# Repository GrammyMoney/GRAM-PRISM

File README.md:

# GRAM PRI$M

# Introduction 
The **PRI$M** is a modular take on the Prism, originally designed by WunWae. It has the standard pinout for firmwares like HayBox and Pico-Rectangle, and is also compatible with more fleshed-out FGC firmwares like GP2040-CE. The key distinctive features between the original Prism and the PRI$M is the USB-C connectivity, and the modular panels that can be replaced and swapped to change the hand layouts without purchasing a whole new controller. With industrial design from GRAM, PCB designed by Quark.Works, this guide goes over a DIY-friendly approach to building and modifying the PRI$M to suit your needs.

**If you would like to support the developers of this project, consider purchasing parts like buttons, PCBs, USB-C to GCC cables, and official GRAM builds at [GRAMCTRL.COM](https://www.gramctrl.com) rather than a fab house.**

Included Files
-
Included in this repo is all the files needed to get started with a PRI$M build:
- **PRI$M Frame .stl files**
- **Aluminum Panel** Gerber files *(5 of 'em!)*
- **PCB Gerbers** for multiple hand layouts and a panelized version for the standard layout

Additional Information
-
If you want more info around GRAM builds, both open source and official builds, please join the [GRAM Digital Controllers Discord](https://discord.gg/6TuHw2r2X4) to ask questions and work with the community! I would love to see people creating new interesting designs, and building upon our initial framework.

Thanks & Acknowledgements
-
There are several people who made this project possible, either directly or indirectly.
- [Quark](https://twitter.com/quark_works), who did the PCB design on this and many other GRAM projects.
- [WunWae](https://twitter.com/WuhnWae), who developed the ergonomics and original Prism design. Thank you for your blessing on this crazy project!
- My life and business partner [BRUISES](https://twitter.com/bruisesxo), who has turned GRAM into what it is today, and had incredible patience with me as I toiled away at my computer late into the night designing this thing.

# Ordering & Customization Guide
While most of these files are universal and can be used at any fab house, **JLCPCB** has become the de-facto standard for DIY box manufacturing. This is due to their hyper-affordable pricing and low minimum order quantity.

Bill of Materials
-
Per GRAM PRI$M, you will need (some files can be made using this repository, but I will link to places to purchase them if you would like to avoid MOQs)
- 1 x PRI$M PCB set *(either panelized, or individual PCBs)*
- 1 x set of PRI$M Aluminum Panels
- 20 x [Kailh Choc V1 switches](https://www.moergo.com/products/kailh-choc-v1-key-switches-red-brown-white-pro-red-20-pack?variant=45328736780561) (Red, Red Pro, and Whites are all great choices)
- 20 x [PG1350 Hotswap Sockets](https://mkultra.click/kailh-hotswap-sockets)
- 20 x Choc v1 keycaps *(I recommend MBK profile)*
- 1 x GRAM PRI$M Frame
- 8 x [M5x0.8 8mm Low-Profile Socket Head Screws](https://www.mcmaster.com/92855A507)
- 2 x [M2.5x0.45 4mm Button Head Screws](https://www.mcmaster.com/catalog/130/3434/97763A412)
- 1 x [4" JST 6-pin Socket to Socket Reversed cable assembly](https://www.digikey.com/en/products/detail/jst-sales-america-inc/A06SR06SR30K102A/9922193)
- 1 x [4" 14-pin FPC Cable](https://www.digikey.com/en/products/detail/molex/0152670295/4427171)

*Optional*
- USB-C to GCC cable for console/adapter play

Tools Needed
-
This guide assumes a level of knowledge on soldering and computer literacy. General tool requirements are:
- Soldering iron
- Solder
- USB-C to USB-A cable
- 3mm hex key/allen wrench
- Pliers
- Patience :)

The PCB
-
***Note: Since the ordering process of the PRI$M is almost identical to the [SLIM](https://github.com/GrammyMoney/GRAM-SLIM), I have used the ordering guide from the SLIM here. You may need to do more repetitions of these steps depending on which PCB you are printing, and you need to do the panel steps for all 5 aluminum panels.***

The PCB Fabrication files should come in the form of a *Gerber ZIP file* and *bom/cpl files* (usually in Excel spreadsheet formats).

Drag them into the "Upload Gerbers" box at JLCPCB and this page will pop up:

Here you can change the color of the PCB. Green is the fastest and cheapest from JLC, but their black PCBs look *siiiiiick*. The only setting I recommend you change is to check "**Yes**" on *Confirm Production file*. This allows for any mistakes to be ironed out by their engineers.

Towards the bottom of the page, you want to turn on the switch for **PCB ASSEMBLY**.

Make sure you are assembling the *Bottom Side* of the PCB, and make sure to set *Confirm Parts Placement* to "**Yes**". None of the advanced options need to be changed.

Upon confirming your PCB Assembly options, you'll be taken to the Assembly wizard. Clicking next will give you a location to upload the *BOM* and *CPL* files (*CPL* is referred to as *Positions* in the GRAM Slim files). Once you click through, you'll be brought to you BOM list.

This will allow you to modify parts if there's any low stock. There's a line at the bottom for CH1-CH21 with some red text. This is for assembling hotswap sockets, which is not recommended for JLC, as you have to preorder them. when you click **next**, continue by clicking *Do not place*.

The wizard looks intimidating, but good news! Since you're confirming part placement, the JLC engineers will fix any errors. Just go ahead and continue.

There you have it! Your PCB is ready to order. As of the time of this writing, a set of 5 assembled boards costs $56.07 before shipping.

The Panels
-
The process of ordering aluminum panels from JLC is similar to the PCB ordering process, but much simpler. Start by dragging the **GRAM Slim Top** Zip file into the JLC upload window. We want an aluminum PCB, 1.6mm. You can choose either white or black coating (white tends to be glossy, black is matte but a fingerprint magnet). 

Under High-spec Options, make sure to remove order number, or else they'll put an ugly serial number on the panel.

Once you save to cart, you'll see this screen:

Here you can add the **GRAM Slim Bottom** Zip file, and it will copy all your settings from the Top panel. Save to cart, and you're ready to check out with your PCBs!

*Note: JLCPCB cannot transact PCB and 3D printing orders together, so place this order, then move on to 3D printing.*

The Frame
-
The frame file is pretty self explanatory. Just go into JLC's 3D printing section, drop the STL file in, and choose your material. I recommend black Resin, but LEDO 6060 is a great, low cost alternative. The only material I recommend against is the textured Nylon options, as the tolerances between the frame and panels are extremely tight, and the texture could interfere with that. make sure the surface finish is set to *sanded*. 

The website will flag some possible errors (Inverted normals, Multi-shells, Possible noise shells) but if you have not modified the .stl file you are good to go. It is also possible that their support contact you about a risk of deformation given the geometry of the workpiece but it is normal and you should reply to the email that you accept the risks.

Need help building your PRI$M? Feel free to join our [Discord](https://discord.gg/gramctrl) for advice from our lovely open source community!

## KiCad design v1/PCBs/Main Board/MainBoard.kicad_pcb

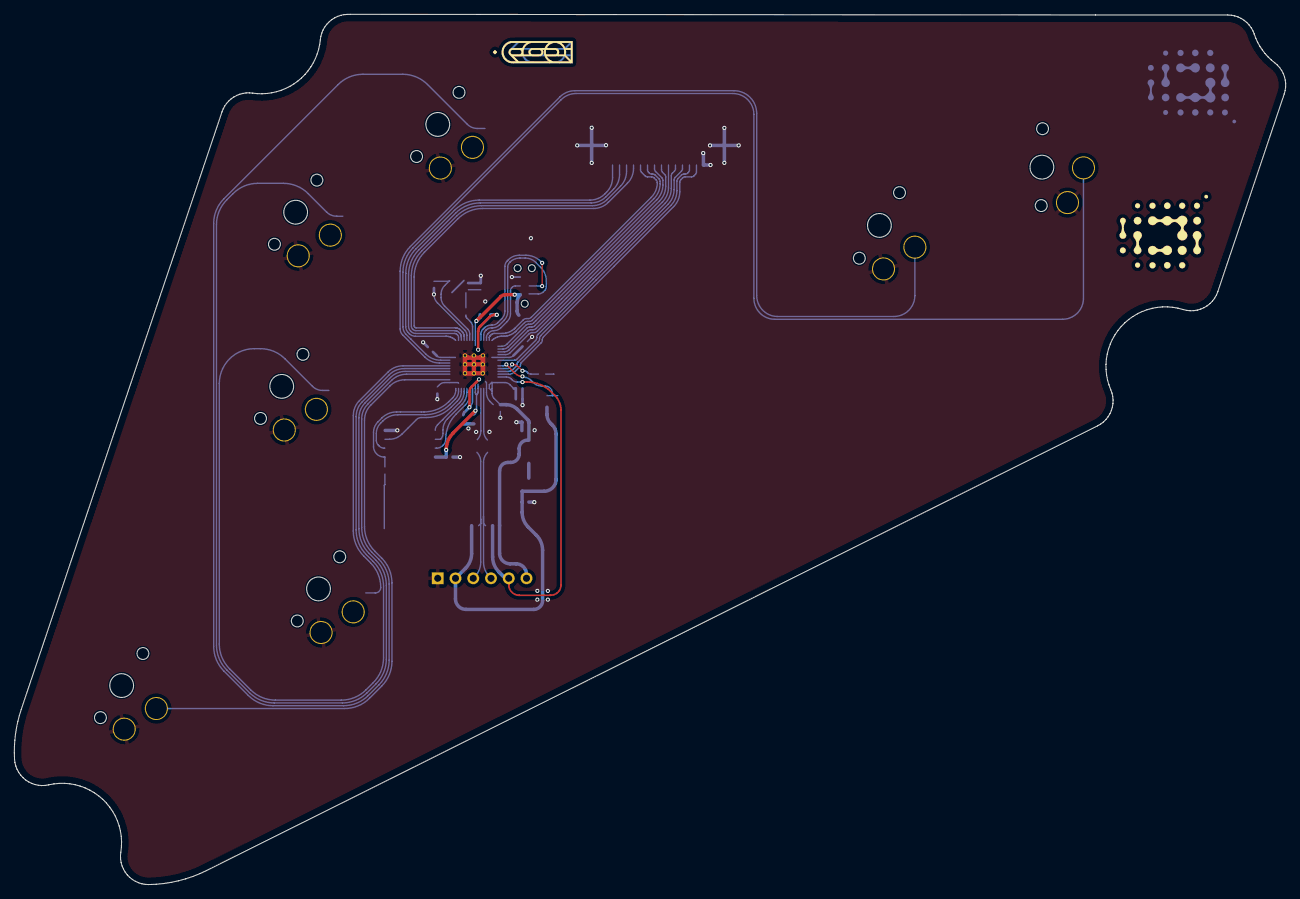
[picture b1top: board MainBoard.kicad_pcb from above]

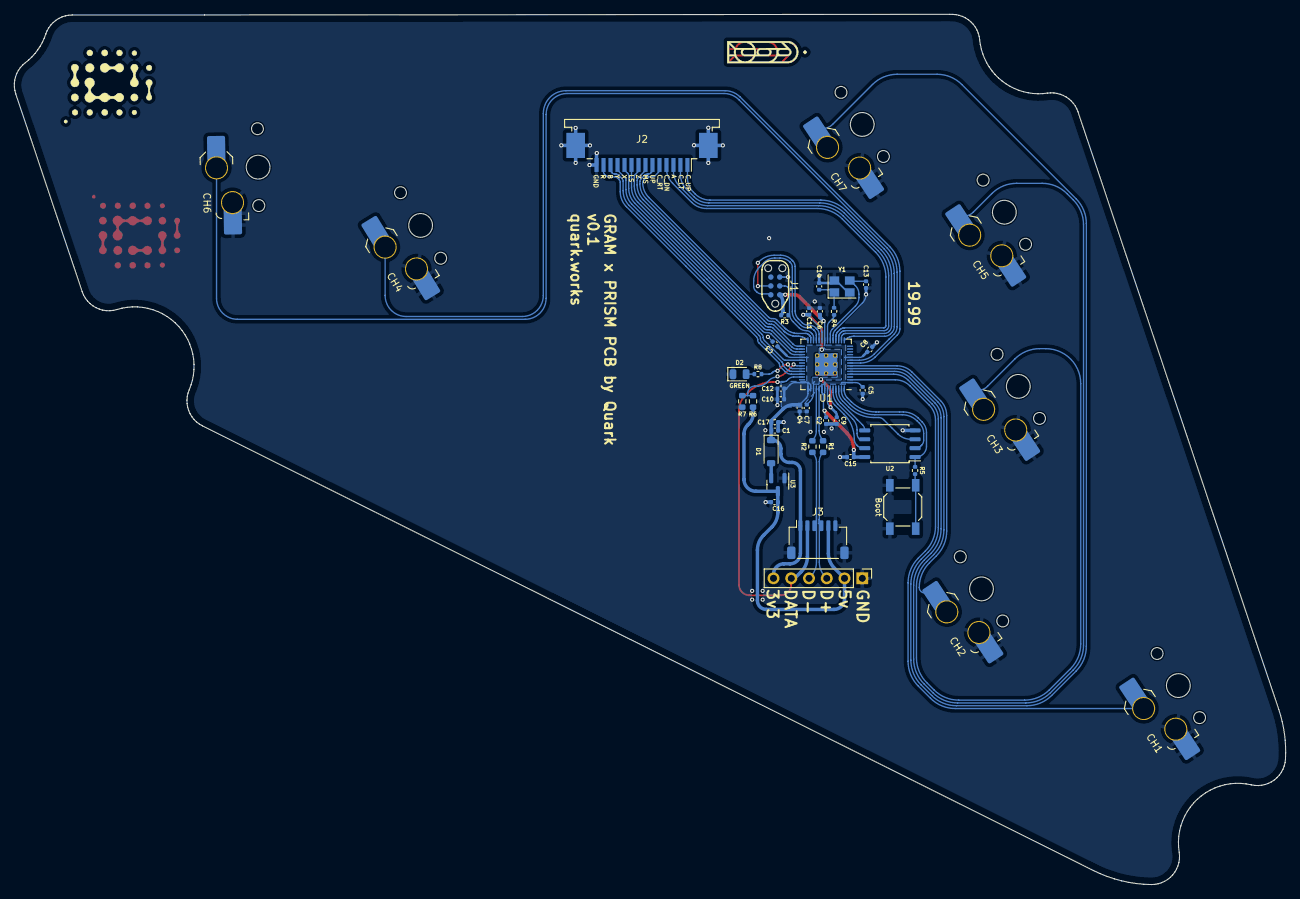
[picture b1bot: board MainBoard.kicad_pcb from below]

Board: 2 copper layers, 181.9 x 124.5 mm, 47 parts (45 on the bottom side), 46 nets.

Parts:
C1: 10uF; C_0402_1005Metric
C2, C7, C16, C17: 1uF; C_0402_1005Metric
C3, C4, C5, C6, C8, C9, C10, C11, C12, C15: 100nF; C_0402_1005Metric
C13, C14: 22pF; C_0402_1005Metric
CH1, CH2, CH3, CH4, CH5, CH6, CH7: choc_SW_HS; SW_choc_v1_HS_1u
D1: Schottky Diode; D_SOD-123
D2: GREEN; LED_0805_2012Metric
H1, H2: qw-logo; qw new logo silk + copper md
H3, H4: 19.99 logo; 1999 logo md
J1: JTAG_TC2030; CON_TC2030_outlined
J2: FFC Connector; TE_1-84953-4_1x14-1MP_P1.0mm_Horizontal
J3: JST Connector; JST_SH_SM06B-SRSS-TB_1x06-1MP_P1.00mm_Horizontal
J4: DuPont Connector; PinHeader_1x06_P2.54mm_Vertical
R1, R2: 27; R_0603_1608Metric
R3, R8: 10k; R_0402_1005Metric
R4, R5: 1k; R_0402_1005Metric
R6: 5.6k; R_0603_1608Metric
R7: 10k; R_0603_1608Metric
SW1: Boot; SW_SPST_SKQG_WithStem
U1: RP2040; RP2040-QFN-56
U2: W25Q128JVS; SOIC-8_5.23x5.23mm_P1.27mm
U3: XC6206; SOT-23
Y1: 12MHz; Crystal_SMD_3225-4Pin_3.2x2.5mm

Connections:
+1V1: C7.1, C9.1, C11.1, U1.23 (DVDD), U1.45 (VREG_VOUT), U1.50 (DVDD)
+3V3: C1.1, C2.1, C3.1, C4.1, C5.1, C6.1, C8.1, C10.1, C12.1, C15.1, C17.2, D1.1 (K), J1.1 (VCC), J3.1, J4.6, R3.1, U1.1 (IOVDD), U1.10 (IOVDD), U1.22 (IOVDD), U1.33 (IOVDD), U1.42 (IOVDD), U1.43 (ADC_AVDD), U1.44 (VREG_VIN), U1.48 (USB_VDD), U1.49 (IOVDD), U2.8 (VCC)
+5V: C16.2, J3.5, J4.2, R6.1, U3.3 (VI)
/D_+: R1.2, U1.47 (D+)
/D_-: R2.2, U1.46 (D-)
/XTAL_O: C14.2, R4.1, Y1.1
/~USB_BOOT: R5.1, SW1.2
A: J2.3, U1.17 (GPIO14)
B: J2.12, U1.38 (GPIO26/ADC0)
CS: R5.2, U1.56 (QSPI_SS_N), U2.1 (~CS)
C_DN: J2.4, U1.18 (GPIO15)
C_LT: J2.2, U1.16 (GPIO13)
C_RT: J2.5, U1.27 (GPIO16)
C_UP: J2.1, U1.15 (GPIO12)
D+: J3.4, J4.3, R1.1
D-: J3.3, J4.4, R2.1
DATA: J3.2, J4.5, U1.40 (GPIO28/ADC2)
DOWN: CH5.2, U1.5 (GPIO3)
GND: C1.2, C2.2, C3.2, C4.2, C5.2, C6.2, C7.2, C8.2, C9.2, C10.2, C11.2, C12.2, C13.1, C14.1, C15.2, C16.1, C17.1, CH1.1, CH2.1, CH3.1, CH4.1, CH5.1, CH6.1, CH7.1, D2.1 (K), J1.5 (GND), J2.14, J2.MP (MountPin), J3.6, J3.MP (MountPin), J4.1, R7.2, SW1.1, U1.19 (TESTEN), U1.57 (GND), U2.4 (GND), U3.1 (GND), Y1.2, Y1.4
L: CH2.2, U1.7 (GPIO5)
LEFT: CH3.2, U1.6 (GPIO4)
LS: J2.9, U1.31 (GPIO20)
M1: CH4.2, U1.8 (GPIO6)
M2: CH6.2, U1.9 (GPIO7)
MS: J2.7, U1.29 (GPIO18)
unnamed: D1.2 (A), U3.2 (VO)
unnamed: D2.2 (A), R8.2
PICO_LED: R8.1, U1.37 (GPIO25)
QSPI_CLK: U1.52 (QSPI_SCLK), U2.6 (CLK)
R: J2.13, U1.39 (GPIO27/ADC1)
RIGHT: CH7.2, U1.4 (GPIO2)
SD0: U1.53 (QSPI_SD0), U2.5 (DI(IO0))
SD1: U1.55 (QSPI_SD1), U2.2 (DO(IO1))
SD2: U1.54 (QSPI_SD2), U2.3 (IO2)
SD3: U1.51 (QSPI_SD3), U2.7 (IO3)
START: CH1.2, U1.2 (GPIO0)
SWCLK: J1.4 (SWCLK), U1.24 (SWCLK)
SWD: J1.2 (SWDIO), U1.25 (SWDIO)
UP: J2.6, U1.28 (GPIO17)
VBUS_SENSE: R6.2, R7.1, U1.36 (GPIO24)
X: J2.10, U1.32 (GPIO21)
XTAL_IN: C13.2, U1.20 (XTAL_IN), Y1.3
XTAL_OUT: R4.2, U1.21 (XTAL_OUT)
Y: J2.11, U1.34 (GPIO22)
Z: J2.8, U1.30 (GPIO19)
~RESET: J1.3 (~RST), R3.2, U1.26 (~RUN)

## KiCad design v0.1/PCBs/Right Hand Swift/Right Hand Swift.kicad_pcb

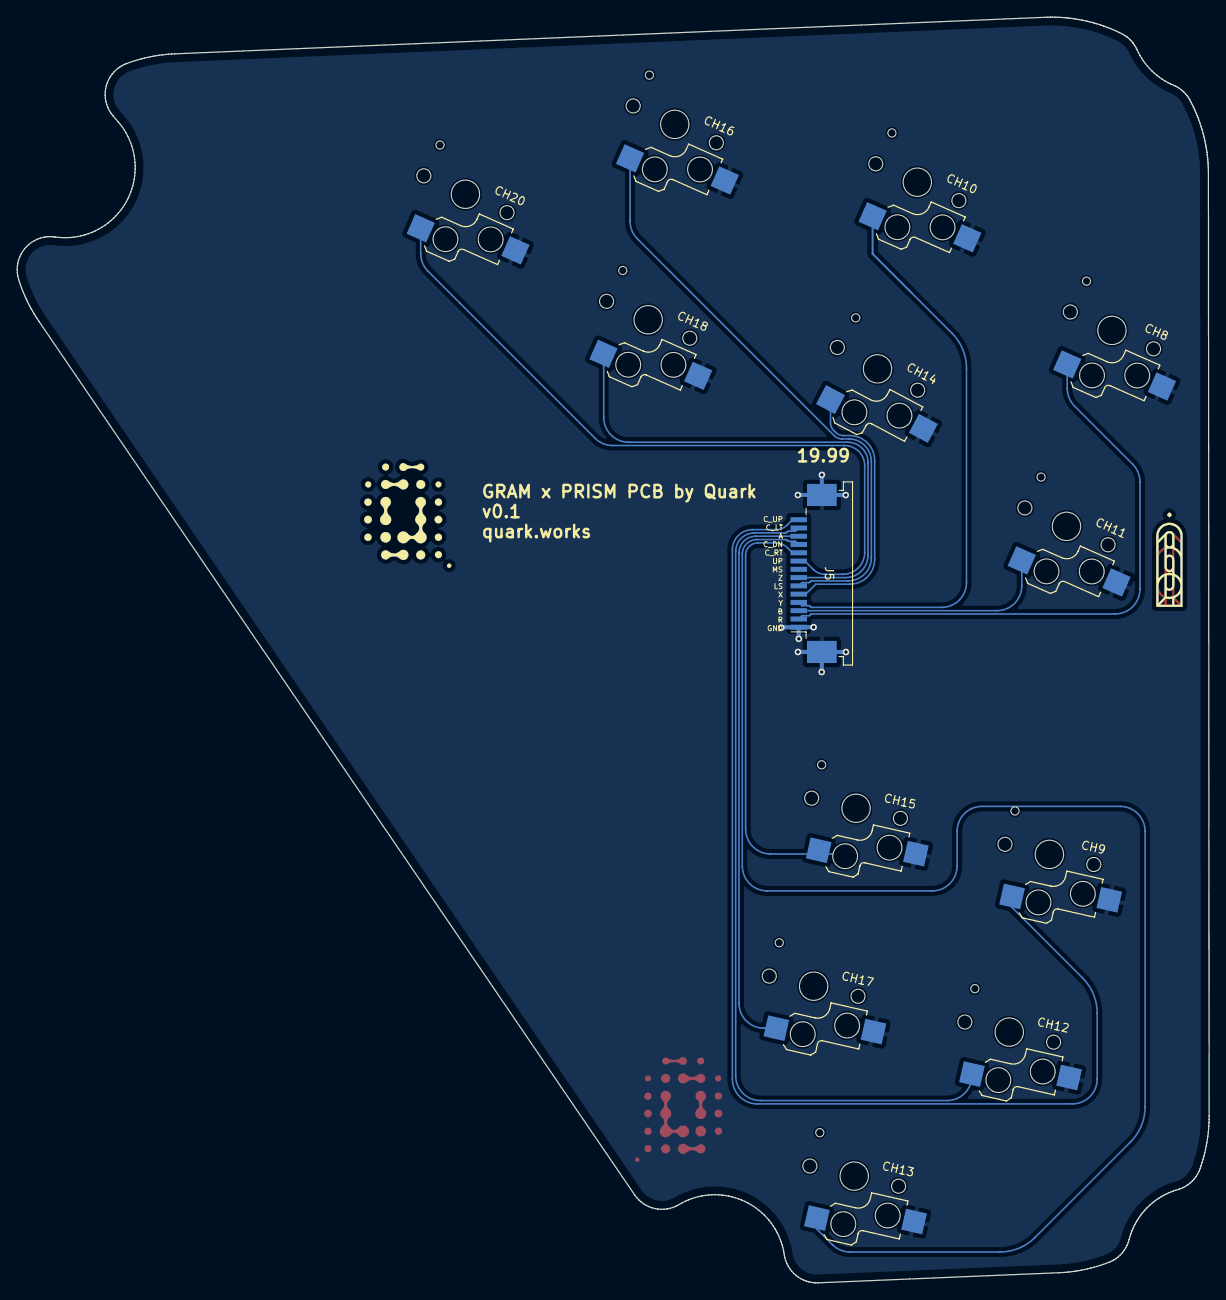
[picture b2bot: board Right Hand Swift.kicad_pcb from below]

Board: 2 copper layers, 144.1 x 153.0 mm, 17 parts (3 on the bottom side), 13 nets.

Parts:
CH8, CH9, CH10, CH11, CH12, CH13, CH14, CH15, CH16, CH17, CH18, CH20: choc_SW_HS; Kailh_socket_PG1350
H5, H6: qw-logo; qw new logo silk + copper md
H7, H8: 19.99 logo; 1999 logo md
J5: FFC Connector; TE_1-84953-4_1x14-1MP_P1.0mm_Horizontal

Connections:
A: CH17.1, J5.12
B: CH11.1, J5.3
C_DN: CH13.1, J5.11
C_LT: CH12.1, J5.13
C_RT: CH15.1, J5.10
C_UP: CH9.1, J5.14
GND: CH8.2, CH9.2, CH10.2, CH11.2, CH12.2, CH13.2, CH14.2, CH15.2, CH16.2, CH17.2, CH18.2, CH20.2, J5.1, J5.MP (MountPin)
LS: CH16.1, J5.6
R: CH8.1, J5.2
UP: CH20.1, J5.9
X: CH14.1, J5.5
Y: CH10.1, J5.4
Z: CH18.1, J5.7

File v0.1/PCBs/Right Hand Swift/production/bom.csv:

Designator,Footprint,Quantity,Value,LCSC Part #
"CH10, CH11, CH12, CH13, CH14, CH15, CH16, CH17, CH18, CH20, CH8, CH9",Kailh_socket_PG1350,12,choc_SW_HS,C5333465
J5,TE_1-84953-4_1x14-1MP_P1.0mm_Horizontal,1,FFC Connector,C376047

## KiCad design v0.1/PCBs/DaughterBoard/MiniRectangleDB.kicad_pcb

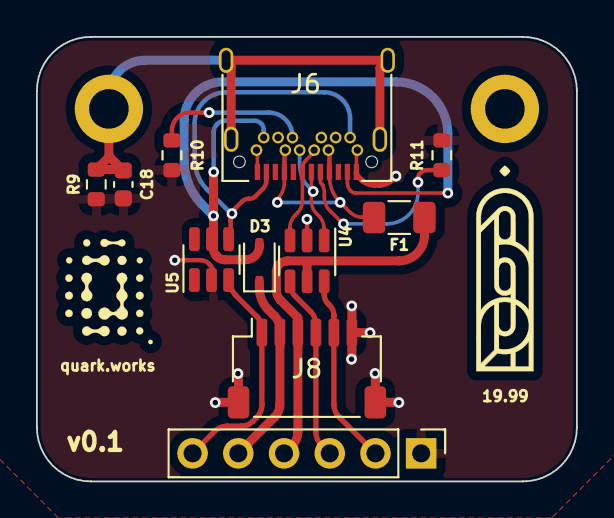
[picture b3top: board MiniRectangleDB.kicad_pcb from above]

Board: 2 copper layers, 30.0 x 24.7 mm, 15 parts (0 on the bottom side), 14 nets.

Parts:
C18: 4.7u; C_0603_1608Metric
D3: Schottky Diode; D_SOD-323
F1: 500 mA; Fuse_1206_3216Metric
H9: MountingHole_Pad; MountingHole_2.2mm_M2_DIN965_Pad
H10: MountingHole; MountingHole_2.2mm_M2_DIN965_Pad
H11: qw logo; qw new logo silk + copper sm
H12: 1999 logo; 1999 logo md
J6: USB C Connector; TYPE-C_24P_QCHT
J7: Conn_01x06; PinHeader_1x06_P2.54mm_Vertical
J8: Conn_01x06; JST_SH_SM06B-SRSS-TB_1x06-1MP_P1.00mm_Horizontal
R9: 1M; R_0603_1608Metric
R10, R11: 5.1k; R_0603_1608Metric
U4, U5: USBLC6-2SC6; SOT-23-6

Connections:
3vCable: D3.2 (A), J6.A2 (TX1+), J6.B2 (TX2+), U5.5 (VBUS)
3vDiode: D3.1 (K), J7.5, J8.2
+5V: F1.2, J7.4, J8.3, U4.5 (VBUS)
D+: J7.2, J8.5, U4.6 (I/O1)
D-: J7.3, J8.4, U4.4 (I/O2)
DATA: J7.6, J8.1, U5.3 (I/O2)
DATABUS: J6.A11 (RX2+), J6.B11 (RX1+), U5.4 (I/O2)
DBUS+: J6.A6 (D+), J6.B6 (D+), U4.1 (I/O1)
DBUS-: J6.A7 (D-), J6.B7 (D-), U4.3 (I/O2)
GND: C18.2, J6.A1 (GND), J6.A12 (GND), J6.B1 (GND), J6.B12 (GND), J7.1, J8.6, R9.1, R10.1, R11.2, U4.2 (GND), U5.2 (GND)
unnamed: F1.1, J6.A4 (VBUS), J6.A9 (VBUS), J6.B4 (VBUS), J6.B9 (VBUS)
unnamed: J6.A5 (CC1), R11.1
unnamed: J6.B5 (CC2), R10.2
unnamed: C18.1, H9.1, J6.S1 (SHIELD), R9.2

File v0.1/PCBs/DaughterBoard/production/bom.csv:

Designator,Footprint,Quantity,Value,LCSC Part #
C18,0603,1,4.7u,C19666
D3,D_SOD-323,1,Schottky Diode,C191023
F1,1206,1,500 mA,C70076
J6,TYPE-C_24P_QCHT,1,USB C Connector,C456013
J8,JST_SH_SM06B-SRSS-TB_1x06-1MP_P1.00mm_Horizontal,1,Conn_01x06,C160405
"R10, R11",0603,2,5.1k,C23186
R9,0603,1,1M,C22935
"U4, U5",SOT-23-6,2,USBLC6-2SC6,C7519

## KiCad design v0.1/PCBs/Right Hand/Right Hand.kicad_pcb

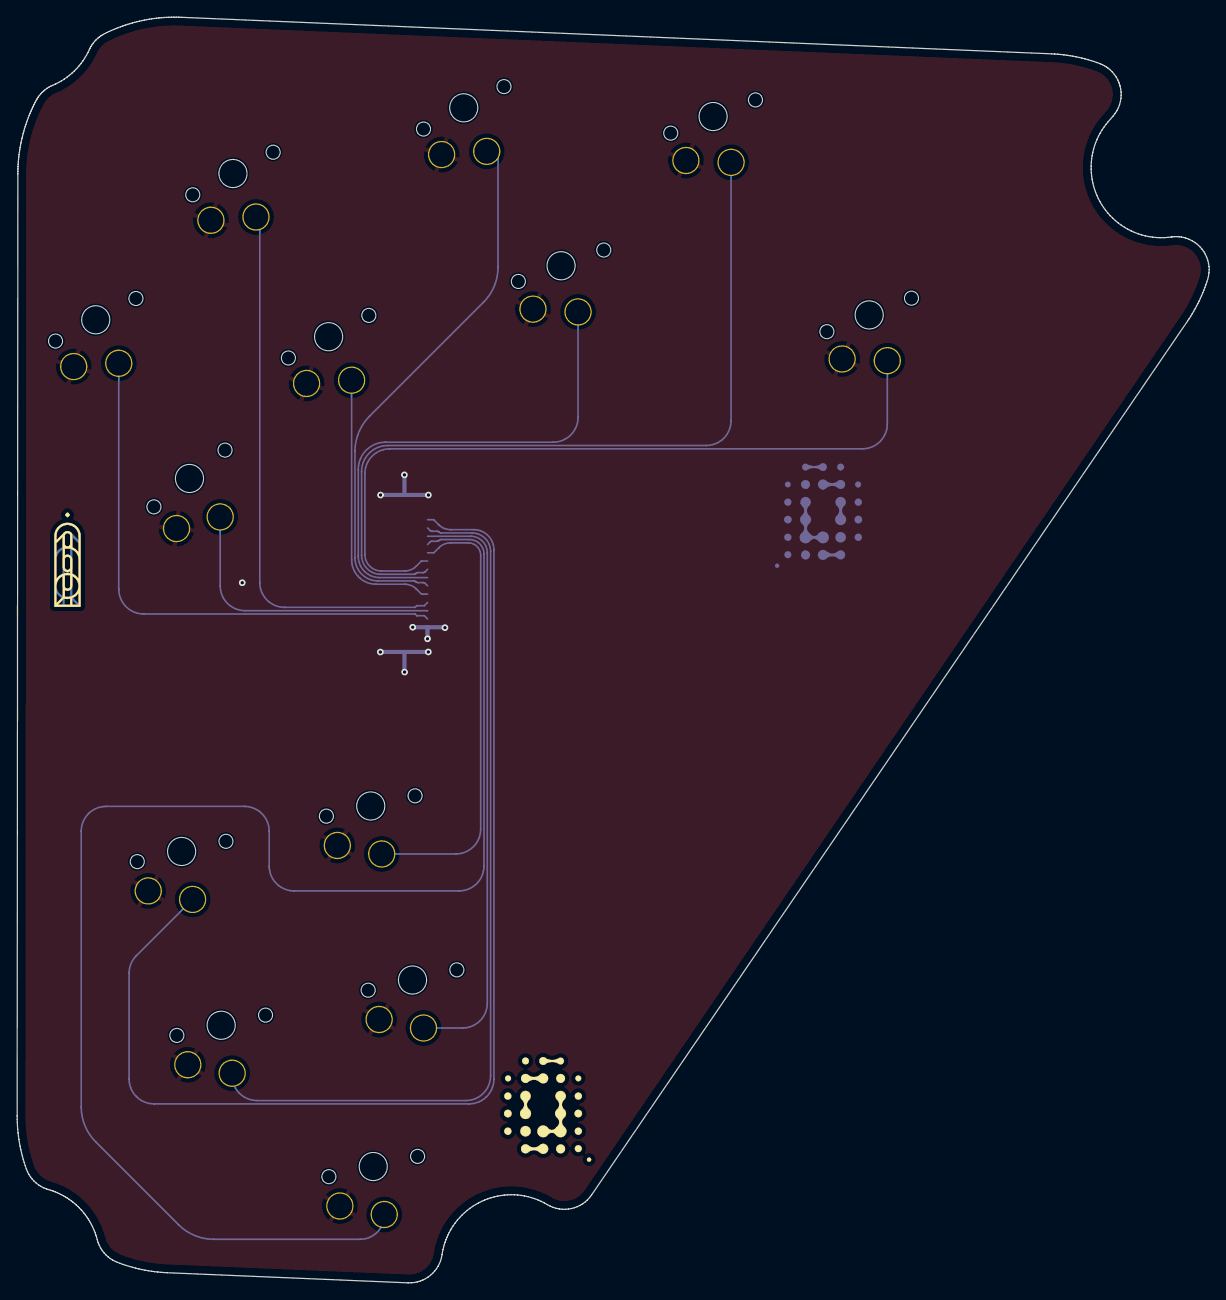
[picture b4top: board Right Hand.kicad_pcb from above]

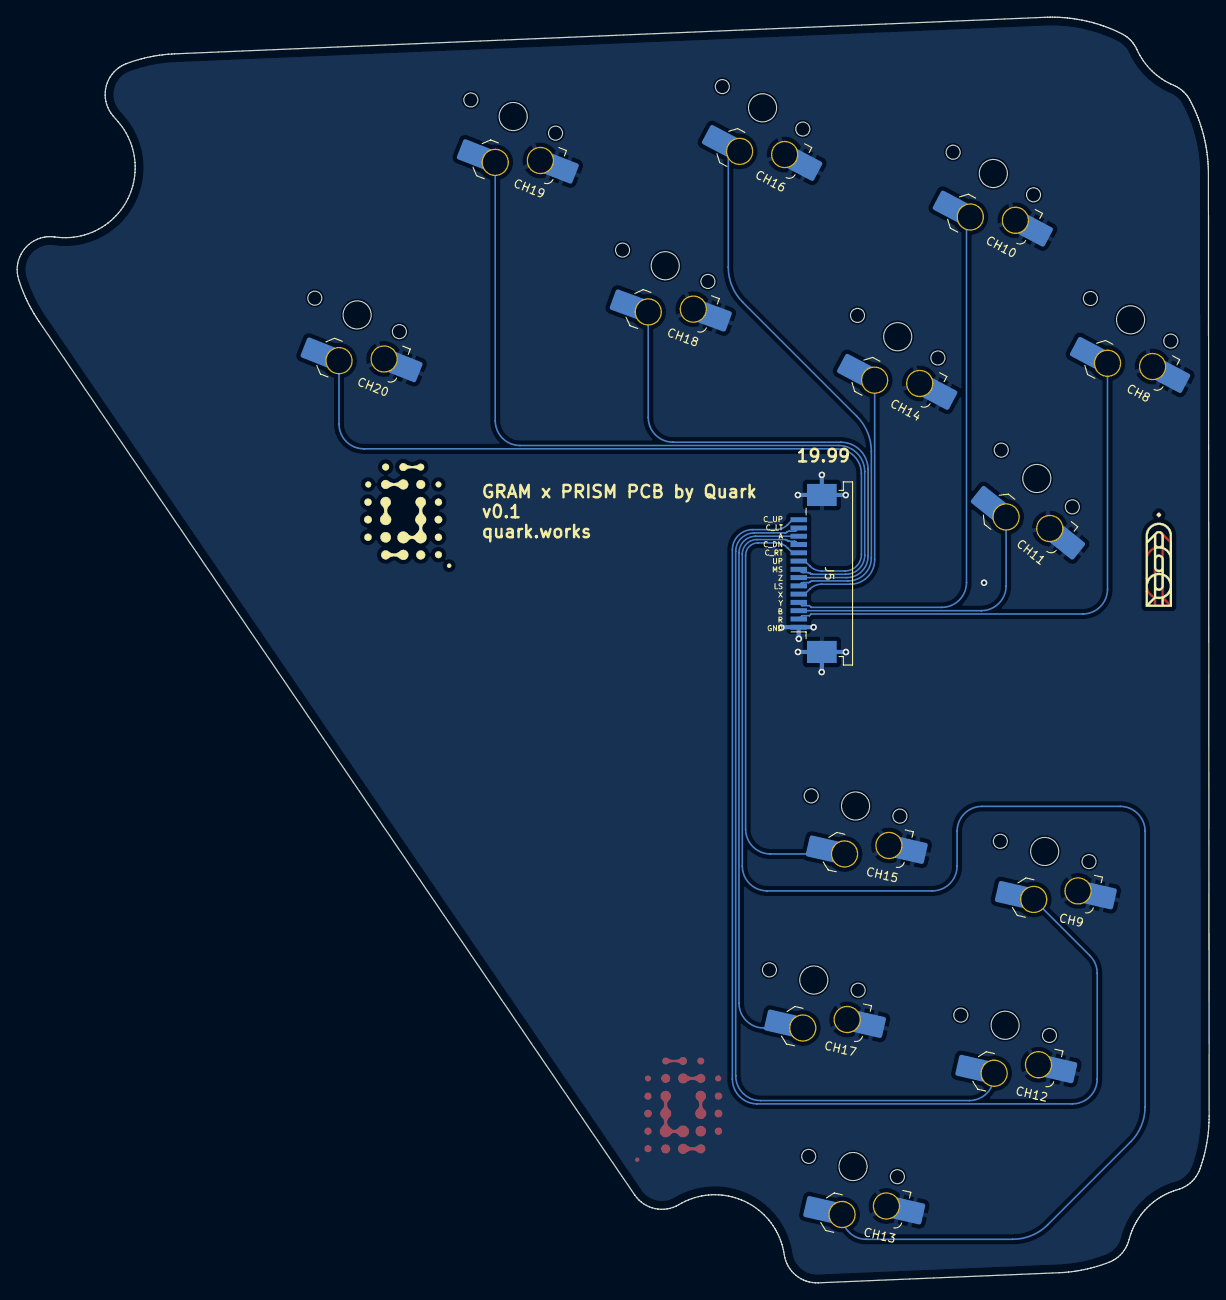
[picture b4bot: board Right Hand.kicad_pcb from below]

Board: 2 copper layers, 144.1 x 153.0 mm, 18 parts (16 on the bottom side), 14 nets.

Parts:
CH8, CH9, CH10, CH11, CH12, CH13, CH14, CH15, CH16, CH17, CH18, CH19, CH20: choc_SW_HS; SW_choc_v1_HS_1u
H5, H6: qw-logo; qw new logo silk + copper md
H7, H8: 19.99 logo; 1999 logo md
J5: FFC Connector; TE_1-84953-4_1x14-1MP_P1.0mm_Horizontal

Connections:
A: CH17.2, J5.12
B: CH11.2, J5.3
C_DN: CH13.2, J5.11
C_LT: CH12.2, J5.13
C_RT: CH15.2, J5.10
C_UP: CH9.2, J5.14
GND: CH8.1, CH9.1, CH10.1, CH11.1, CH12.1, CH13.1, CH14.1, CH15.1, CH16.1, CH17.1, CH18.1, CH19.1, CH20.1, J5.1, J5.MP (MountPin)
LS: CH16.2, J5.6
MS: CH19.2, J5.8
R: CH8.2, J5.2
UP: CH20.2, J5.9
X: CH14.2, J5.5
Y: CH10.2, J5.4
Z: CH18.2, J5.7

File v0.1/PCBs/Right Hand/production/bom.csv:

Designator,Footprint,Quantity,Value,LCSC Part #
"CH10, CH11, CH12, CH13, CH14, CH15, CH16, CH17, CH18, CH19, CH20, CH8, CH9",SW_choc_v1_HS_1u,13,choc_SW_HS,C5333465
J5,TE_1-84953-4_1x14-1MP_P1.0mm_Horizontal,1,FFC Connector,C376047

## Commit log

2023-09-26 First panelized revision
2023-09-26 Removed some temporary files
2023-09-26 Added individual production files
2023-09-26 Added right hand swift and production files
2023-09-28 Added finalized production files for frame and aluminum panels
2023-09-29 Adjusted choc to the preferred footprint
2023-09-29 Adjusted Swift right side to the preferred footprint
2023-10-11 Adjusted daughterboard pinout and drill hole error on right hand
2023-10-12 Fixed MX, MY and C-Down
2023-10-18 expanded holes
2024-01-04 updated readme for public release
2024-01-04 Cleaned up for public release
2024-02-08 [Documentation] Adding a note about the possible warnings that can happen with JLCPCB for 3D printing of the frame
2024-02-09 added extra panel DXFs
2024-06-21 Create LICENSE
2024-06-22 Updated JST connector orientation
2024-06-30 Updated FFC connector and Fuse part number
2024-07-01 Adjusted hot swap sockets positioning
2024-07-07 Added M2.5 Screws (thanks biz_fish!)
